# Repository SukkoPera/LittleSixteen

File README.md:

# LittleSixteen

LittleSixteen is an Open Hardware remake of the Commodore 16, 116 and Plus/4 home computers, featuring many improvements over the original design.

## Summary
While this project started as a simple redrawing of the C16 schematics, it has now evolved into what could be considered the flagship member of the 264 family of Commodore computers, since it has all the characteristics of the other models [^nospeech] and bears a full array of extra features and improvements, while keeping full compatibility with them.

The new goal of this project is to allow anyone to build a very significant home computer from the '80s from scratch, only using parts that can be found on the market [^almost]. The design is fully through-hole so no particular soldering skills are required for the assembly. The estimated cost of ALL materials (case and power supply included) for a single complete machine is around 250-300€.

## Differences and Improvements
The original Commodore 16 was the victim of several cost-cutting measures during its design phase. Its target price was $99 and Commodore still had to have some margin on that, so they really had to spare every cent they could and they went as far as not mounting the decoupling capacitors for a few chips which happened to have another one "close enough". Thus, a further goal of this project was to undo all of those measures and make the design as clean as possible, while also improving on it.

### Modifications introduced in V4
The goal of V4 was to make LittleSixteen an improved Plus/4 clone, rather than a C16 clone.

- 100% Plus/4 compatible User Port.
- 512 kB Hannes-style RAM expansion (which can be reduced to 256 kB through a single jumper for compatibility reasons).
- 2 ROM banks, each of which can carry the whole set of ROMs: KERNAL + BASIC + Function ROMs.
- Onboard SID (either 6581 or 8580 + Optional Digifix) + 3rd joystick port (SID audio is mixed with the TED/Ext audio with configurable volume but direct dedicated output is also available).
- Direct TED audio output connector.
- Joystick swapper.
- Ability to replace keyboard MOS 6529 with 74x273 (so that 6529 can be recycled for User Port, but that one as well can be replaced with a 74x654).
- Removed FB13 in order to reduce luma/chroma crosstalk and improve video quality.
- Pin header with all tape signals (think Internal Tapuino).
- Pin header with all IEC signals (think Internal SD2IEC).

### Modifications introduced in V3
In V3 we started making improvements to the board. The reasoning behind every modification is detailed on the [Development Blog](https://hackaday.io/project/182543-littlesixteen-commodore-16-mainboard), so I'll be pretty terse here.

- Switched to external power regulation, using the C64 power circuit and power supply: drastically reduces the heat inside the case, which is one of the main CPU/TED failure causes.
- Added current-limiting resistors on all ports exposing power pins: this will avoid short-circuiting the power supply, whatever you do on the external connectors.
- Added internal Joystick port buffers: this is basically like having two [OpenC16JoyAdapter](https://github.com/SukkoPera/OpenC16JoyAdapter)s built into the machine, preventing the TED pins to be directly exposed on the joystick ports, which is another common cause of TED failures. It also gives the ports a fixed ground, allowing the use of "advanced" joysticks with autofire functionalities for instance, which require power from the machine.
- Joystick ports now use DB-9 (more properly: DE-9) connectors, just like any other machine of the era: you can now use your favourite C64/Amiga joystick on your C16.
- Similarly, the Datassette port was changed to the C64-style edge connector. An adapter to keep connecting the 1531 Datassette is trivial to make.
- Moved to the C64 power switch, since this can still be found on the market and is functionally equivalent.
- The CPU can now either be an original 7501/8501 or even a 6510, thanks to [Andrew Challis's adapter](http://hackjunk.com/2017/06/23/commodore-16-plus-4-8501-to-6510-cpu-conversion/) being integrated on the board.
- In a similar fashion, the board can either directly accept an original MOS 251641 PLA or [Daniël Mantione's GAL16V8-based reimplementation](https://www.freepascal.org/~daniel/c16pla/).
- The design flaw that prevented the usage of cartridge-based RAM expansions was fixed: you can now plug in an [OpenC16RamExpansion](https://github.com/SukkoPera/OpenC16RamExpansion) without the internal RAM fighting with it.
- Actually that might not even be necessary, as the board now directly supports either 16 or 64 kB of internal RAM.
- Since the RF modulator is basically useless these days, a [replacement circuit](https://github.com/mbarszcz-pcb/c64-rf-modulator-replacement) was integrated on the board, providing either Luma+Chroma (say S-Video) or Composite Video.
- Added the possibility of combining the KERNAL and BASIC in a single all-in-one ROM: this allows replacing the original power-hungry chips with a single W27C512, which can also incorporate the Plus/4 function ROMs.
- ESD protection was improved on all ports.
- The track and ground plane layout were optimized in a few places in order to reduce noise and crosstalk.

While the comprehensive switch of connectors to the C64 counterparts might be frowned upon, it was done because [C64-style cases](https://icomp.de/shop-icomp/en/shop/product/c64c-case.html) are still in production and this way LittleSixteen V3 will fit them just perfectly, yielding the ability to build new C16s from scratch, which is another one of our goals.

### Modifications introduced in V2
V2 was meant to be a 1:1 copy of the original board with some essential improvements requiring minimum effort. The goal was to have a proved-working design we could start from in order to make improvements.

- The original board was probably laid out by hand and a lot of tracks were drawn with arbitrary slopes. I have sticked to only 45 degrees tracks, which of course means I could not follow the original tracks exactly, but I tried to stay as close to them as possible and to keep all the "visual hints" that allow identifying a track quickly. I must admit I'm quite satisfied of the end result, to be honest.
- I used my usual track widths and via sizes (plus some new values for the larger tracks), I didn't bother figuring out what sizes the original board used.
- All tracks were laid out "by eye", which means with *reasonable* - not *maniacal* - accuracy to the original design. Most care was taken in the positioning of components that ought to be in a certain position (i.e.: screw holes and I/O connectors), to ensure drop-in replaceability. Other components and tracks are "more or less" there, but as the board was wholly laid out from scratch by hand, don't expect sub-millimeter accuracy.
- The footprints for all DIP chips use "long pads". This makes them easier to solder and more solid to the board should you need to rework them. This forced a few tracks running very close to the original pads to be slightly offset away.
- Some footprints are slightly longer/larger/wider pitch/whatever than the originals, so that I could use ready-made KiCad libraries.
- Footprints for the connectors and modulator were taken from [StormTrooper's Plus/4 remake](https://github.com/StormTrooper/Commodore-Plus4), without checking them for correctness.
- I didn't bother to create the right footprint for the original power connector, as there's no point in wasting time for some item that is nowhere to be found these days. I used a much more common one instead. Same goes for the inductor.
- I didn't pay much attention to the silkscreen, many labels can probably be placed better, but I added a description for every IC, like it or not.
- Proper footprints were added for all the protection diodes that Commodore forcibly retrofitted on real boards (See D96-99).
- With the C16, Commodore went as far as saving a few cents by not mounting the decoupling capacitors for a few chips. They left the pads on the board but removed all silkscreen indications. These were restored and assigned random numbers.
- The ground fill is autogenerated by KiCad, so it won't match the original exactly (not even close).
- Probably there's something more I've forgotten.

If you don't like any of the above, feel free to fix it yourself and [submit a Pull Request](https://github.com/SukkoPera/LittleSixteen/pulls).

## Testing
V3  and V4 of the board were throughly tested by project collaborator Edoardo Auteri, as you can read on the [Development Blog](https://hackaday.io/project/182543/log/202804-how-to-make-the-changes-that-change-everything). In his words:

> The machine works flawlessly providing superior audio and video performance, low power consumption and compatibility with the 1530 Datassette Unit (C2N model), SD2IEC, Atari joysticks and pads.

## Assembly
If you want to build your own board, **please make sure read the assembly notes on [the Wiki](https://github.com/SukkoPera/LittleSixteen/wiki) carefully!**

Note that there are different pages for different revisions of the board.

## Releases
If you want to get this board produced, you are recommended to get [the latest release](https://github.com/SukkoPera/LittleSixteen/releases) rather than the current git version, as the latter might be under development and is not guaranteed to be working.

Every release is accompanied by its Bill Of Materials (BOM) file and any relevant notes about it, which you are recommended to read carefully.

**I am not providing ready-to-use gerber files**. If all you want is **to get boards made, I would really appreciate if you did so [in a way that supports the project](#support-the-project)**.

## License
The LittleSixteen documentation, including the design itself, is copyright &copy; SukkoPera 2019-2025 and is licensed under the [Creative Commons Attribution-NonCommercial-ShareAlike 4.0 International License](https://creativecommons.org/licenses/by-nc-sa/4.0/).

This documentation is distributed *as is* and WITHOUT ANY EXPRESS OR IMPLIED WARRANTIES whatsoever with respect to its functionality, operability or use, including, without limitation, any implied warranties OF MERCHANTABILITY, SATISFACTORY QUALITY, FITNESS FOR A PARTICULAR PURPOSE or infringement. We expressly disclaim any liability whatsoever for any direct, indirect, consequential, incidental or special damages, including, without limitation, lost revenues, lost profits, losses resulting from business interruption or loss of data, regardless of the form of action or legal theory under which the liability may be asserted, even if advised of the possibility or likelihood of such damages.

## Support the Project
If you want to get some boards manufactured, you can get them from PCBWay through this link:

You get my gratitude and cheap, professionally-made and good quality PCBs, I get some credit that will help with this and [other projects](https://www.pcbway.com/project/member/shareproject/?bmbid=41100). You won't even have to worry about the various PCB options, it's all pre-configured for you!

Also, if you still have to register, [you can use this link](https://www.pcbway.com/setinvite.aspx?inviteid=41100) to get some bonus initial credit (and yield me some more).

You can also buy me a coffee if you want:

## Thanks
- My father, for buying me my C16 when I was 8, my first computer ever. This project is dedicated to his memory.
- Amiwell, for giving me a free C16 that I used to trace a lot of connections.
- [StormTrooper](https://github.com/StormTrooper/Commodore-Plus4) for his similar project about the Plus/4, which is where many of the footprints and 3D models used in this project come from.
- J. F. Gomez, for the [3D model of the Barrel jack](https://grabcad.com/library/dc-power-jack-5-5mm-x-2-1mm-2-54mm-pitch-1).
- [Edoardo Auteri](https://github.com/kinmami), for his invaluable advice on analog stuff and for fully assembling the first prototype and testing it thoroughly.
- Gordon Fecyk AKA Great White Retro, for beta-testing, making videos of his builds and spreading the word.
- Last but not least, thanks to [PCBWay](https://www.pcbway.com) for sponsoring the project and providing us with free prototypes of V3.

[^nospeech]: Ok, ok... No V364 speech support, I'll admit!
[^almost]: Almost, the CPU, TED and Expansion port connector must be recovered somehow.

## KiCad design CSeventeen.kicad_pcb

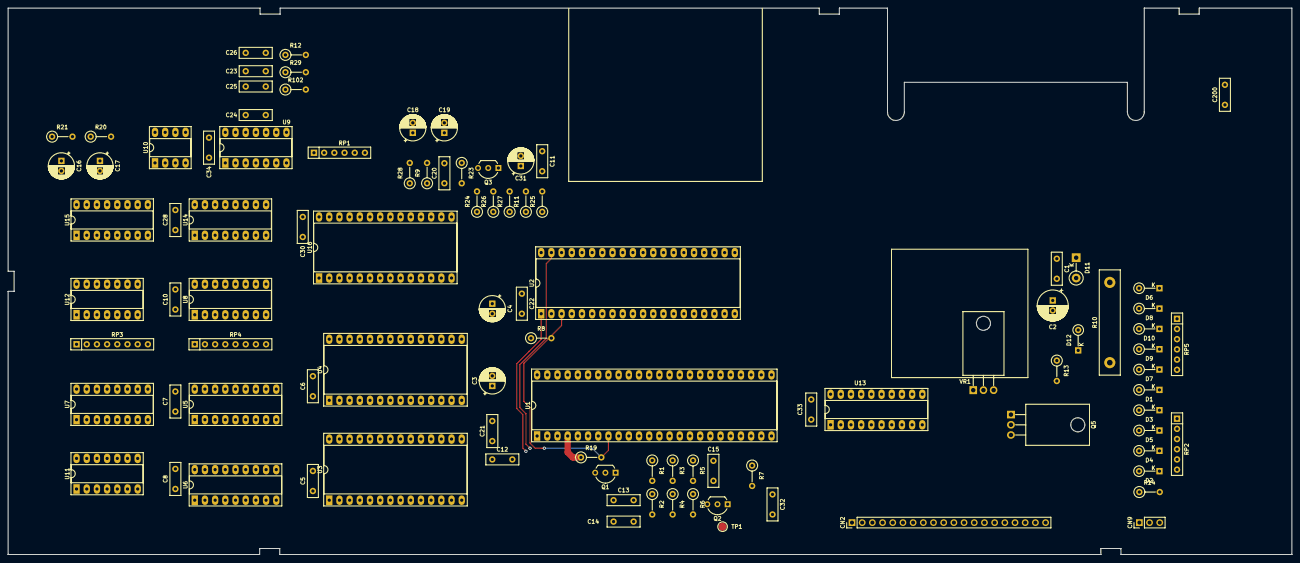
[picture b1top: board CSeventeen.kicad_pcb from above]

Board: 2 copper layers, 320.0 x 136.2 mm, 98 parts (0 on the bottom side), 109 nets.

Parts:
C1, C5, C6, C10, C11, C21, C22, C26, C28, C30, C33, C34: 100n; C_Disc_D8.0mm_W2.5mm_P5.00mm
C2: 47u/25V; CP_Radial_D7.5mm_P2.50mm
C3, C4, C16, C18, C19, C31: 10u/25V; CP_Radial_D6.3mm_P2.50mm
C7, C8, C200: 220n; C_Disc_D8.0mm_W2.5mm_P5.00mm
C12: 22p; C_Disc_D8.0mm_W2.5mm_P5.00mm
C13: 220p; C_Disc_D8.0mm_W2.5mm_P5.00mm
C14: 150p; C_Disc_D8.0mm_W2.5mm_P5.00mm
C15: 10p; C_Disc_D8.0mm_W2.5mm_P5.00mm
C17: 1u/16V; CP_Radial_D6.3mm_P2.50mm
C20: 10n; C_Disc_D8.0mm_W2.5mm_P5.00mm
C23, C24, C25: 470p; C_Disc_D8.0mm_W2.5mm_P5.00mm
C32: 100p; C_Disc_D8.0mm_W2.5mm_P5.00mm
CN2: KEYBOARD_HEADER; PinHeader_1x20_P2.54mm_Vertical
CN9: LED_CONNECTOR; PinHeader_1x03_P2.54mm_Vertical
D1, D2, D3, D4, D5, D6, D7, D8, D9, D10: 1N914; D_DO-35_SOD27_P5.08mm_Vertical_KathodeUp
D11: 1N914; D_DO-41_SOD81_P5.08mm_Vertical_KathodeUp
D12: 6.8V; D_DO-35_SOD27_P5.08mm_Vertical_KathodeUp
Q1, Q2, Q3: 2SC1815; TO-92_Inline_Wide
Q5: 2SD880; TO-220-3_Horizontal_TabDown
R1, R23: 10k; R_Axial_DIN0207_L6.3mm_D2.5mm_P5.08mm_Vertical
R2: 4.7k; R_Axial_DIN0207_L6.3mm_D2.5mm_P5.08mm_Vertical
R3, R7, R13, R14: 470; R_Axial_DIN0207_L6.3mm_D2.5mm_P5.08mm_Vertical
R4: 220; R_Axial_DIN0207_L6.3mm_D2.5mm_P5.08mm_Vertical
R5: 18k; R_Axial_DIN0207_L6.3mm_D2.5mm_P5.08mm_Vertical
R6: 1.5k; R_Axial_DIN0207_L6.3mm_D2.5mm_P5.08mm_Vertical
R8, R24, R28: 1k; R_Axial_DIN0207_L6.3mm_D2.5mm_P5.08mm_Vertical
R9: 12k; R_Axial_DIN0207_L6.3mm_D2.5mm_P5.08mm_Vertical
R10: 20/5W; R_Box_L26.0mm_W5.0mm_P20.00mm
R11, R21, R25: 100k; R_Axial_DIN0207_L6.3mm_D2.5mm_P5.08mm_Vertical
R12, R19: 3.3k; R_Axial_DIN0207_L6.3mm_D2.5mm_P5.08mm_Vertical
R20: 47k; R_Axial_DIN0207_L6.3mm_D2.5mm_P5.08mm_Vertical
R26, R27: 240; R_Axial_DIN0207_L6.3mm_D2.5mm_P5.08mm_Vertical
R29: 100; R_Axial_DIN0207_L6.3mm_D2.5mm_P5.08mm_Vertical
R102: 330; R_Axial_DIN0207_L6.3mm_D2.5mm_P5.08mm_Vertical
RP1: 1k; R_Array_SIP6
RP2, RP5: 3.3k; R_Array_SIP6
RP3, RP4: 68; R_Array_SIP8
TP1: CLOCK_TESTPOINT; TestPoint_Pad_D2.0mm
U1: MOS_7360_TED; DIP-48_W15.24mm_Socket_LongPads
U2: MOS_8501; DIP-40_W15.24mm_Socket_LongPads
U3: 23128_BASIC; DIP-28_W15.24mm_Socket_LongPads
U4: 23128_KERNAL; DIP-28_W15.24mm_Socket_LongPads
U5, U6: 4416; DIP-18_W7.62mm_Socket_LongPads
U7, U8: 74LS257; DIP-16_W7.62mm_Socket_LongPads
U9: 74LS06; DIP-14_W7.62mm_Socket_LongPads
U10: NE555; DIP-8_W7.62mm_Socket_LongPads
U11: 74LS125; DIP-14_W7.62mm_Socket_LongPads
U12: 74LS02; DIP-14_W7.62mm_Socket_LongPads
U13: MOS_6529; DIP-20_W7.62mm_Socket_LongPads
U14: 74LS139; DIP-16_W7.62mm_Socket_LongPads
U15: 74LS175; DIP-16_W7.62mm_Socket_LongPads
U16: MOS_251641_PLA; DIP-28_W15.24mm_Socket_LongPads
VR1: 7805; TO-220-3_Horizontal_TabDown

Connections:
+9V: C1.1, D11.1, Q5.2, R10.2, R13.1, VR1.1
/RAM/m0: RP3.2, U5.14, U6.14
/RAM/m1: RP3.4, U5.13, U6.13
/RAM/m2: RP3.6, U5.12, U6.12
/RAM/m3: RP3.8, U5.11, U6.11
/RAM/m4: RP4.2, U5.8, U6.8
/RAM/m5: RP4.4, U5.7, U6.7
/RAM/m6: RP4.6, U5.6, U6.6
/RAM/m7: RP4.8, U5.10, U6.10
AEC: U1.35, U2.4
BA: U1.34, U2.2
CASSETTE: U11.10, U16.16
EXT_AUDIO: R25.1, R28.2
GND: C1.2, C2.2, C3.2, C4.2, C5.2, C6.2, C7.2, C8.2, C10.2, C11.2, C12.2, C14.2, C16.2, C17.2, C20.2, C21.2, C22.2, C23.1, C24.1, C25.1, C26.1, C28.2, C30.2, C32.2, C33.2, C34.2, CN2.4, CN9.2, D12.1, Q2.1, R2.2, R4.2, R6.2, R9.2, R11.1, R25.2, R27.1, U1.24, U2.20, U3.14, U3.20, U4.14, U4.20, U5.1, U5.18, U6.1, U6.18, U7.8, U7.15, U8.8, U8.15, U9.7, U10.1, U11.1, U11.4, U11.7, U12.7, U13.10, U14.8, U15.8, U16.14, U16.19, VR1.2
KEYPORT_CS: U13.19, U16.12
MUX: U1.9, U2.23, U7.1, U8.1, U16.27
unnamed: C13.1, Q1.3, R1.2, R2.1
unnamed: C13.2, C14.1, Q1.1, R4.1
unnamed: C15.1, Q2.3, R5.2, R6.1
unnamed: C15.2, Q1.2, R3.2
unnamed: C16.1, R20.2, U10.6, U10.7
unnamed: C17.1, R21.2, U10.2
unnamed: C18.1, C19.1, C20.1, R9.1, R23.2, R24.2
unnamed: C18.2, R28.1
unnamed: C19.2, R8.1
unnamed: C24.2, R29.2
unnamed: C25.2, R12.2, U11.9
unnamed: C31.1, R26.1, R27.2
unnamed: C31.2, R11.2
unnamed: CN9.1, CN9.3, R14.2
unnamed: D1.1, RP2.2
unnamed: D2.1, RP2.6
unnamed: D3.1, RP2.3
unnamed: D4.1, RP2.5
unnamed: D5.1, RP2.4
unnamed: D12.2, Q5.3, R13.2, U9.6
unnamed: RP1.4, U9.4
unnamed: RP1.3, U9.8
unnamed: Q3.1, R26.2
unnamed: Q2.2, R7.2, TP1.1, U1.14
unnamed: Q3.3, R24.1
unnamed: RP3.1, U7.4
unnamed: RP3.3, U7.7
unnamed: RP3.5, U7.9
unnamed: RP3.7, U7.12
unnamed: RP4.1, U8.4
unnamed: RP4.3, U8.7
unnamed: RP4.5, U8.9
unnamed: RP4.7, U8.12
unnamed: U12.1, U15.9
unnamed: U12.2, U16.11
unnamed: U12.4, U14.14
unnamed: U12.5, U15.6
unnamed: U12.6, U12.9, U16.13
unnamed: U12.8, U15.11
unnamed: U12.10, U14.13
unnamed: U14.2, U15.2
unnamed: U14.3, U15.15
unnamed: U16.9, U16.10
PHI0: U1.12, U2.1, U16.8
R_~W: U1.7, U2.39, U5.4, U6.4, U12.3, U13.1
SERIAL_RESET: U9.1, U9.3, U10.3
SND: R8.2, U1.33
VCC: C2.1, C3.1, C4.1, C5.1, C6.1, C7.1, C8.1, C10.1, C21.1, C22.1, C26.2, C28.1, C30.1, C32.1, C33.1, C34.1, D11.2, Q3.2, R1.1, R3.1, R5.1, R7.1, R10.1, R12.1, R14.1, R19.1, R20.1, R21.1, R23.1, R102.1, RP1.1, RP2.1, RP5.1, U1.4, U2.5, U3.1, U3.27, U3.28, U4.1, U4.27, U4.28, U5.9, U6.9, U7.2, U7.16, U8.14, U8.16, U9.14, U10.4, U10.8, U11.14, U12.14, U13.20, U14.16, U15.16, U16.28, VR1.3
a0: U1.3, U2.6, U3.10, U4.10, U7.3, U15.4
a1: U1.2, U2.7, U3.9, U4.9, U7.6, U15.13
a2: U1.1, U2.8, U3.8, U4.8, U7.10, U15.5
a3: U1.48, U2.9, U3.7, U4.7, U15.12
a4: U1.47, U2.10, U3.6, U4.6, U8.3, U16.6
a5: U1.46, U2.11, U3.5, U4.5, U8.6, U16.5
a6: U1.45, U2.12, U3.4, U4.4, U8.10, U16.4
a7: U1.44, U2.13, U3.3, U4.3, U8.13, U16.3
a8: U1.43, U2.14, U3.25, U4.25, U7.5, U16.25
a9: U1.42, U2.15, U3.24, U4.24, U7.11, U7.13, U16.24
a10: U1.41, U2.16, U3.21, U4.21, U7.14, U16.21
a11: U1.40, U2.17, U3.23, U4.23, U8.2, U16.22
a12: U1.39, U2.18, U3.2, U4.2, U8.5, U16.2
a13: U1.38, U2.19, U3.26, U4.26, U8.11, U16.23
a14: U1.37, U2.21, U16.26
a15: U1.36, U2.22, U16.7
d0: U1.25, U2.38, U3.11, U4.11, U5.2, U13.18
d1: U1.26, U2.37, U3.12, U4.12, U5.3, U11.5, U13.17
d2: U1.27, U2.36, U3.13, U4.13, U5.15, U11.2, U11.8, U13.16
d3: U1.28, U2.35, U3.15, U4.15, U5.17, U13.15
d4: U1.29, U2.34, U3.16, U4.16, U6.2, U13.14
d5: U1.30, U2.33, U3.17, U4.17, U6.3, U13.13
d6: U1.31, U2.32, U3.18, U4.18, U6.15, U13.12
d7: U1.32, U2.31, U3.19, U4.19, U6.17, U13.11
k0: D1.2, D6.2, RP5.2, U1.15
k1: D2.2, D7.2, RP5.6, U1.16
k2: D3.2, D8.2, RP5.3, U1.17
k3: D4.2, D9.2, RP5.5, U1.18
k6: D5.2, U1.21
k7: D10.2, RP5.4, U1.22
p0: U2.30, U9.13
p1: U2.29, U9.11
p2: U2.28, U9.9
p3: U2.27, U9.5
p4: C23.2, U2.26
p6: R29.1, RP1.5, U2.25, U9.10
p7: RP1.6, U2.24, U9.12
~BASIC_CS1: U3.22, U14.4
~CAS: U1.11, U5.16, U6.16
~CS0: U1.5, U14.1
~CS1: U1.6, U14.15
~IRQ: R19.2, U1.8, U2.3
~KERNAL_CS1: U4.22, U14.12
~RAS: U1.10, U5.5, U6.5, U16.20
~RESET: RP1.2, U2.40, U9.2, U15.1

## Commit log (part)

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2019-11-27 Add RAM and Expansion Port
2019-11-27 Add RP3/4
2019-11-27 Use better library for 74x257's and add power
2019-11-27 Forgotten libs...
2019-11-27 Add misc sheet
2019-11-27 Add reset circuit
2019-11-28 Add Datassette and power
2019-11-28 Connect Datassette signals to I/O pins
2019-11-28 Add Serial Bus
2019-11-28 Add U9/U11 power
2019-11-28 Fix label
2019-11-29 Add ROMs
2019-11-30 Add Selection circuit
2019-12-02 Add PLA
2019-12-02 Add AV output and... we're done!
2020-01-19 Fix schematics here and there
2020-01-19 Remove unmeaningful PCB
2020-01-19 CSeventeen -> LittleSixteen
2020-01-19 Add README and license
2020-01-19 Add TED HW Manual
2020-01-20 Add schematics pdf
2020-01-20 Map RP3/4 and add (J)D1/2
2020-10-04 Fix some errors pointed out by bwack in #1
2020-10-25 cleanup keyboard and joystick schematics
2020-12-20 Fix for KiCad 5.1.7
2021-07-13 Fix board dimensions
2021-07-13 Add ceramics
2021-07-13 Add diodes
2021-07-13 Add electrolytics
2021-07-13 Start working on PCB
2021-07-13 Add pin headers
2021-07-13 Use 3d models from github.com/StormTrooper/Commodore-Plus4
2021-07-13 Add EMI filters and ferrites
2021-07-13 CSeventeen -> LittleSixteen (PCB)
2021-07-13 Make notches in board outline
2021-07-13 Add Page Settings
2021-07-13 Who remembers?
2021-07-13 Fix ferrite 3d models
2021-07-13 Add some tracks
2021-07-13 Route a lot of RAM-related tracks & more
2021-07-14 Add missing lib
2021-07-14 Working on PCB...
2021-07-14 Complete routing of expansion connector
2021-07-14 A whole looooooot of work
2021-07-15 Laid out data bus and muuuuch more stuff
2021-07-15 Guess what
2021-07-15 Almost there...
2021-07-16 A little work
2021-07-16 Add some coppazones
2021-07-16 One last connection missing!
2021-07-16 Add holes and exposed copper areas
2021-07-19 Turn ferrites the right way
2021-07-20 Routing is finished, somehow Still needs embellishment
2021-07-20 Fix overlapping courtyards
2021-07-20 Adjust power rails
2021-07-20 Fix all courtyard issues and work a bit on ground plane
2021-07-20 Work a bit on silkscreen and add logo
2021-07-20 Remove fp-info-cache
2021-07-20 Add extra decoupling caps There are actually (unnamed) footprints for these on an actual board, I guess they were skipped for cost saving reasons, sigh...
2021-07-21 Further work on silkscreen and add connector measurements
2021-10-27 Fix orientation of some ferrites
2021-10-27 Add fp-info-cache to .gitignore
2021-10-28 Fix position of CN6 and M1
2021-10-28 Fix position of CN3 and CN7
2021-10-28 Fix tracks to the right of modulator and add 3D models for EMI filters
2021-10-30 Add protection diodes and improve clarity
2021-10-30 Lots of tidying up
2021-10-30 More tidying up
2021-10-30 Add p4 protection diodes
2021-10-31 Final touches
2021-10-31 Move POR to misc, review some notes
2021-10-31 Call this V2, as V1 was schematics-only
2021-10-31 Update schematics PDF
2021-10-31 Ready for V2
2022-10-24 Switch to TSR 2-2450 regulator
2022-10-24 Add support for PLA16V8
2022-10-24 Split kbd+joy into separate sheets
2022-10-24 Fit alt socket for 6510 Still some fine work TBD
2022-10-24 Add buffers on joystick ports - WIP
2022-10-24 Minor layout fixes
2022-10-24 Improvements on the ground plane
2022-10-24 Restore JD1/2
2022-10-24 Add note on 6510 CPU
2022-10-24 Switch to Kycon MiniDIN connectors
2022-10-24 Add a way to disable internal RAM from expansion connector
2022-10-24 Add 16/64k RAM switch
2022-10-24 Add motto
2022-10-24 Add 3D models of all chips and move logo
2022-10-24 Fine-tuning
2022-10-24 Add modulator replacement
2022-10-24 Add ability to use a single 64k (EEP)ROM
2022-10-24 Fix +9V fill
2022-10-24 Make holes for cart connector metal cover
2022-10-24 Fix joystick buffers ^___^
2022-10-24 Position power c'tors, button and reset more accurately Footprints for power and reset buttons need to be checked again
2022-10-24 Add board dimensions
2022-10-24 Rename extra caps and switch to full THT power circuit Well, there's one SMD component, but it's optional :)
2022-10-24 You've reeeeeaaaaaaallyyyyy maaaaade theee graaaaadeee
2022-10-24 Work on ground plane
2022-10-24 Add better ESD protection for Serial Connector
2022-10-24 Move R/W track to U13 to improve ground plane
2022-10-24 Add credits
2022-10-24 Add some protection diodes we'd overlooked
2022-10-24 This is groooooouuund controooool to Maaaajooor Toooom
2022-10-24 Drown COLOR and SYNC_LUM into an OCEAN OF GROUND
2022-10-24 Add diode+resistor to control Datassette motor when using 6510
2022-10-24 Position some components better
2022-10-24 More honing
2022-10-24 Improve left connector
2022-10-24 Fix power switch
2022-10-24 Switch D90 to THT footprint
2022-10-24 Improve power zones
2022-10-24 Add current-limiting resistors on joystick ports and start working on silkscreen
2022-10-24 Add ferrite on regulator output
2022-10-24 Add credits for good old @bwack
2022-10-24 LOOKING GOOOOOD!
2022-10-24 Get rid of J1
2022-10-24 Add internal Tape/IEC connector
2022-10-24 Add better ESD protection for Datassette Connector and some notes
2022-10-24 Use footprints for DIN connector that we can actually find on the market
2022-10-24 Improve ground plane
2022-10-24 Do not leave input pins of spare gate floating
2022-10-24 Improve left connector (again, but this time I like it)
2022-10-24 Add ESD protection on joystick ports
2022-10-24 Minor fix
2022-10-24 Add current-limiting resistor on Datassette port
2022-10-24 Tidy up silkscreen
2022-10-24 Bump version
2022-10-24 Add jumper on RAMEN
2022-10-24 Add current-limiting resistor on A/V connector Note that there's no ferrite on the +5V pin...
2022-10-24 /RAMEN should go to the RAMs' /OE, not to the MUXs'...
2022-10-24 Various minor fixes
2022-10-24 Isolate crystal from top ground layer
2022-10-24 Add ferrite on A/V power out
2022-10-24 Switch joystick ports to DB9 connectors Not sure the power switch still fits. Fixing screws might touch protection diodes, too.
2022-10-24 Use C64 power switch
2022-10-24 More cosmetic fixes
2022-10-24 Switch to C64-style Power Connector
2022-10-24 Add PCBWay logo
2022-10-24 Enlarge drill holes to 0.9mm in order to make it possible to use ZIF sockets
2022-10-24 Restore IC labels
2022-10-24 Close JP8 by default
2022-10-24 Final touch
2022-10-24 Cosmetic fixes
2022-10-24 Add C94 and C95, remove C108
2022-10-24 Move U92
2022-10-24 Last cosmetic fixes?
2022-10-24 Add text for U90
2022-10-24 Add forgotten file
2022-10-24 Use C64 Datassette Connector This forced us to remove the internal Tapuino/SD2IEC connector, sigh
2022-10-24 Use local Ferrite_Bead_Small symbol
2022-10-24 Use clearer diode footprint
2022-10-24 Wire R96 in a way that makes sense
2022-10-24 Remove unused footprint
2022-10-24 Isolate video ground
2022-10-24 Updats schematics
2022-10-24 Fix silkscreen for D12
2022-10-24 Add resistor pack type
2022-10-24 Design a working alternative for MOS6529
2022-10-24 Add working alternative for 6529 - Thanks @kinmami!
2022-10-24 Improve video output - Thanks @kinmami!
2022-10-24 Remove unmasked border, round corners, add cart connector labels
2022-10-24 Work on silkscreen
2022-10-31 Update renders
2023-02-15 Add userport schematics and enlarge board
2023-02-16 Add SID schematics
2023-02-18 Place components on board
2023-02-25 Connect SID audio output
2023-02-25 GNDA -> VGND
2023-02-25 Q81/82 -> 2SC1815 (for uniformity)
2023-02-25 Realign board on grid Edges are no longer lined on 0.20mm though, sigh
2023-02-25 Routing in progress
2023-05-06 Well yeah maybe
2023-05-07 Mmmmh
2023-07-10 -10!
2023-07-10 -4...
2023-07-11 -2!!!
2023-07-11 Add SID power circuit, to be placed - MISSION IMPOSSIBLE!
2023-07-12 SID Power is almost there
2023-07-12 Closer and closer...
2023-07-17 Replace joystick buffers with '245s This was done for economy of scale, as we already have other '245s onboard
2023-07-17 I'm your lover, I'm you Z-E-R-O!
2023-07-18 Cleaning up...
2023-07-18 ... and cleaning...
2023-07-18 Almost there
2023-07-19 Yeah
2023-07-19 C15 -> 10nF
2023-07-19 Cutout for cheap power switches
2023-07-19 Sure
2023-07-19 SID area should be ok now
2023-07-19 YEAH!
2023-07-20 Fill space used by former /RAMEN track
2023-07-20 Add Open Source ad
2023-07-20 Some work on silkscreen, more to do but let's call this RC1
2023-07-20 Minor changes
2023-07-20 Refine zones
2023-07-20 Remove FB13 For the rationale on this mod, see https://plus4world.powweb.com/forum/46948
2023-07-20 Make all ferrite/EMI filter pins on the same axis
2023-07-20 Make most ICs HCT
2023-07-20 Ground plane refinement
2023-07-20 Make JP12 a real jumper
2023-07-20 Add Expansion Port cover 3d model
2023-07-22 Switch to 2-pin header for joyswap
2023-07-22 Ground plane finesse - RC3, ready for review by @kinmami
2023-07-22 More ground plane finesse
2023-07-22 Clean up some tracks
2023-07-22 Add pad for grounding ACIA crystal
2023-07-22 Remove bottom pad from Q5, just leave some unfilled space around screw hole
2023-07-22 Replace L1 with ferrite
2023-07-22 Add thin border without soldermask
2023-07-23 Add TED direct audio output header (Experimental)
2023-07-24 Prolong screw holes so that they reach the unmasked border
2023-07-24 Improve ground under FB95
2023-07-24 Fix first issues reported by @kinmami
2023-07-25 Add internal IEC/TAPE headers
2023-07-25 Second round of issues reported by @kinmami
2023-07-25 Add testpoints
2023-07-26 Work on SID area, better isolate LUMA/CHROMA
2023-07-27 Third round of fixes by @kinmami
2023-07-27 Final silkscreen touches
2023-07-27 J1 -> CN14
2023-07-27 U21 -> HCT
2023-07-29 Move some labels
2023-07-30 Add ROM bank switcher (All-in-one ROM only)
2023-07-31 Hone ROM bank switcher
2023-07-31 Reduce copper on top edge in order to allow for beveling
2023-08-01 Rework tracks around U90
2023-08-11 Rationalize BOM There should be no significant changes on both schematics on PCB, just some values and something on the silkscreen
2023-08-11 Rationalize capacitor footprints & BOM
2023-08-12 Add note on some components
2023-08-12 Make C83 10uF
2023-08-12 Minor fixes
2023-08-12 Fix tracks around U14
2023-11-17 Fix protruding track
2024-02-05 Add keyboard power jumper and remove pin 2 from keyboard connector
2024-02-05 VTED -> VSID, sigh...
2024-02-23 Add footprint for single oscillator
2024-02-23 Add GAL equations
2024-03-03 Fix missing PHI2 This was due to another stupid bug in WinCUPL, sigh...
2024-07-21 Add GAL equations for limiting RAM to 256kB
2024-07-21 Replace /BRESET on Expansion Port and User Port with /RESET This was an oversight we probably introduced in V3 which makes it impossible for the Expansion Port and User Port to reset the machine thro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
2024-07-21 Add pull-up network for keyboard buffer Not strictly necessary, boards seems to work fine without, but in principle it should be there
2024-07-21 Final touches for the previous job
2024-07-25 Add a note about datassette Sense This led to https://github.com/sweetlilmre/tapuino/pull/52
2024-08-07 Add P7 option for Tape Sense jumper, in order to replicate Plus/4 J8/J9
2024-08-11 Add jumper to select which reset signal is brought to IEC connector
2024-08-18 Fix screw holes for C16 case
2024-08-31 Move some tracks around
2024-11-13 Add RAM size jumper So we no longer need to reflash PLA2 to change it!
2024-11-13 Couldn't finely hone
2025-01-02 New composite video circuit
2025-01-03 Fix video tracks
2025-01-04 Fix all points from #15
2025-01-04 Switch to polyfuses on userport and to ferrites for FB38/39/40
2025-02-09 Back to MiniDIN-7 connector for Datassette
2025-02-09 Fix D12 orientation
2025-02-09 Fix C15
2025-02-09 Fix R96
2025-02-09 Fix silkscreen errors on U5/6 and U13
2025-02-22 Round corners
2025-02-22 Add cutoff for Chinese power switch
2025-06-21 Fix some P/Ns
2025-06-22 Fix joystick switcher
2025-06-22 R37 -> 220
2025-06-22 RP4 -> 3.3k Thanks @gordonfpanam!
2025-06-22 Fix footprint for U17
2025-06-22 Use resettable fuses everywhere we do current limiting
2025-06-22 Do not short JP81/82 by default
2025-06-23 Cut R19 out from Clock Generator box and move led connector up
2025-06-29 Minor fixes + P/N updates
2025-10-18 Update README with project details and improvements
2025-10-18 Update README to reflect project changes and improvements
2025-10-20 Remove stale schematics
